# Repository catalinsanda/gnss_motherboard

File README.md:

# gnss_motherboard
Carrier board for ESP32 &amp; UM980 boards

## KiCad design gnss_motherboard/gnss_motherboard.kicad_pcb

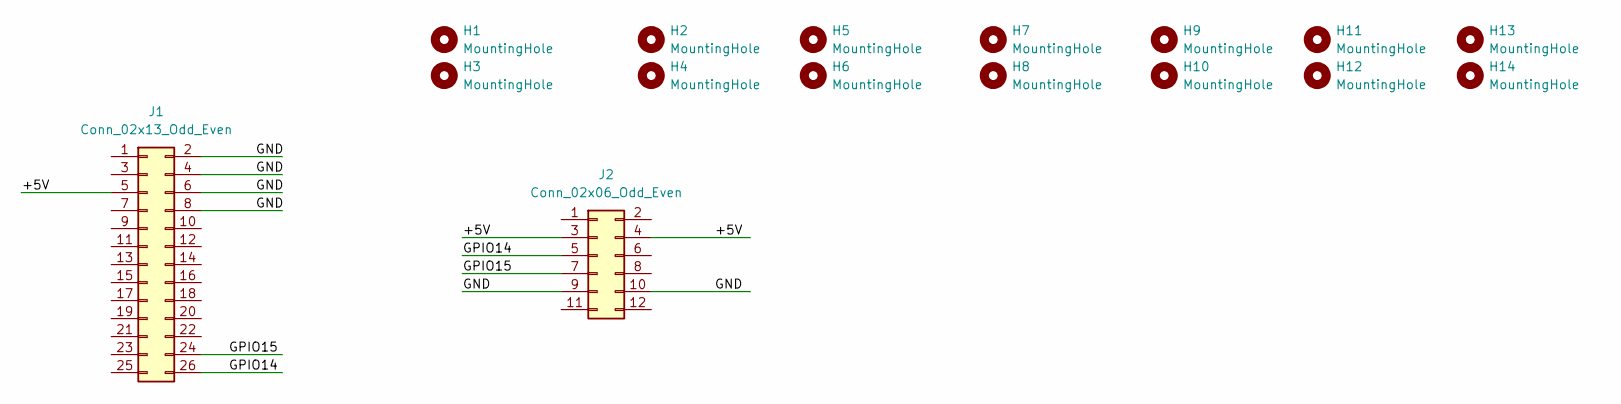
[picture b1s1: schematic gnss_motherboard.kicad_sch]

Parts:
H1, H2, H3, H4, H5, H6, H7, H8, H9, H10, H11, H12, H13, H14: MountingHole; MountingHole_3.2mm_M3_DIN965
J1: Conn_02x13_Odd_Even
J2: Conn_02x06_Odd_Even

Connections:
/+5V: J1.5, J2.3, J2.4
/GND: J1.2, J1.4, J1.6, J1.8, J2.9, J2.10
/GPIO14: J1.26, J2.5
/GPIO15: J1.24, J2.7

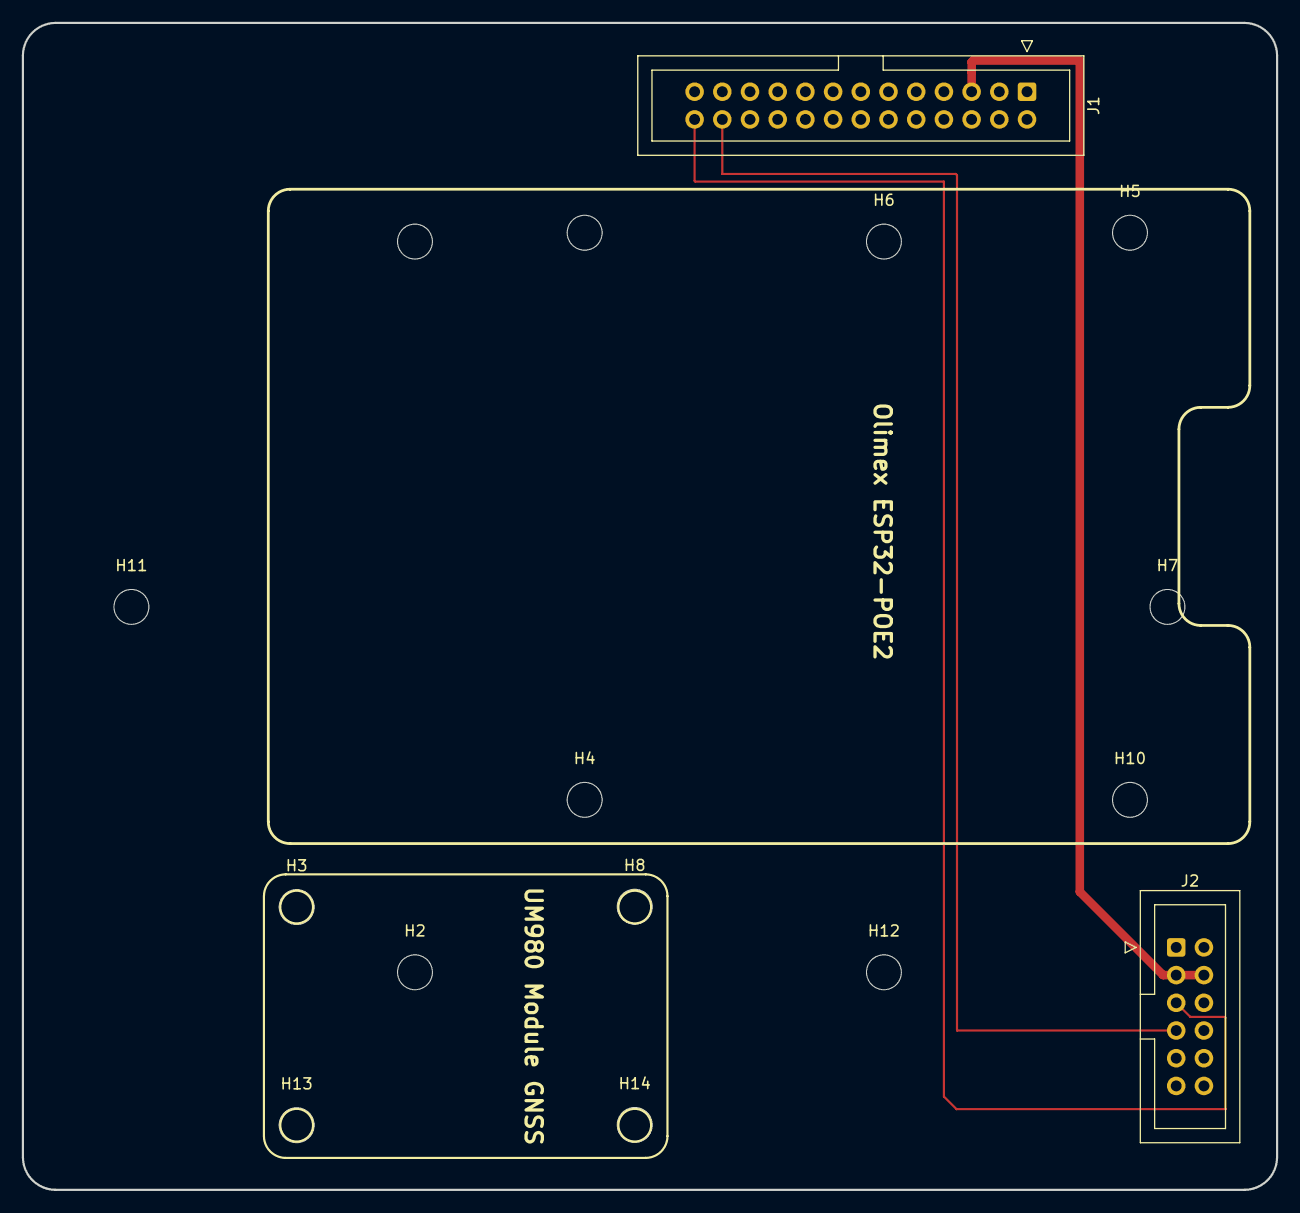
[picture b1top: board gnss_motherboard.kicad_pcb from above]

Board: 2 copper layers, 115.0 x 107.0 mm, 16 parts (0 on the bottom side), 4 nets.

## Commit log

2025-06-17 Add files
